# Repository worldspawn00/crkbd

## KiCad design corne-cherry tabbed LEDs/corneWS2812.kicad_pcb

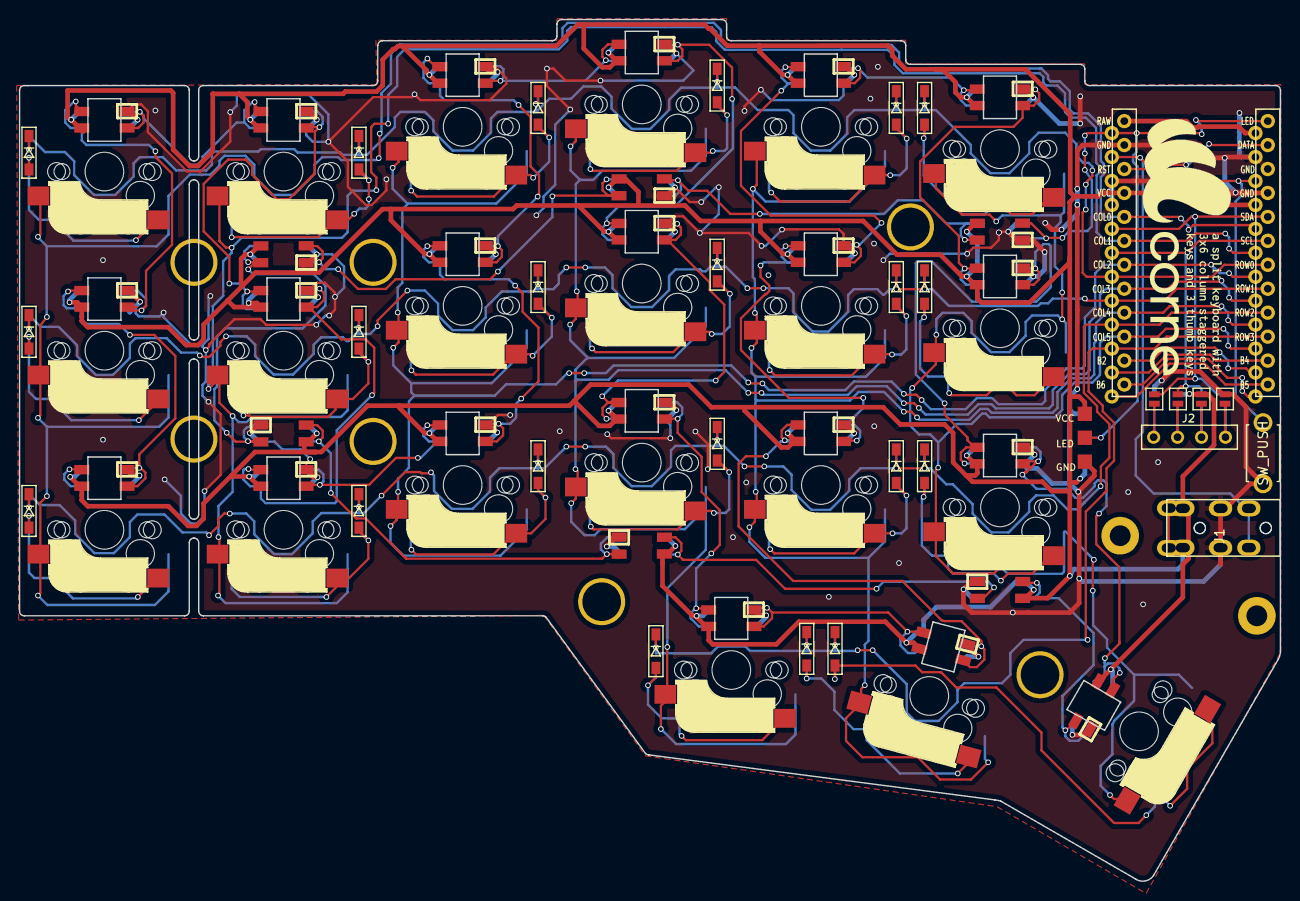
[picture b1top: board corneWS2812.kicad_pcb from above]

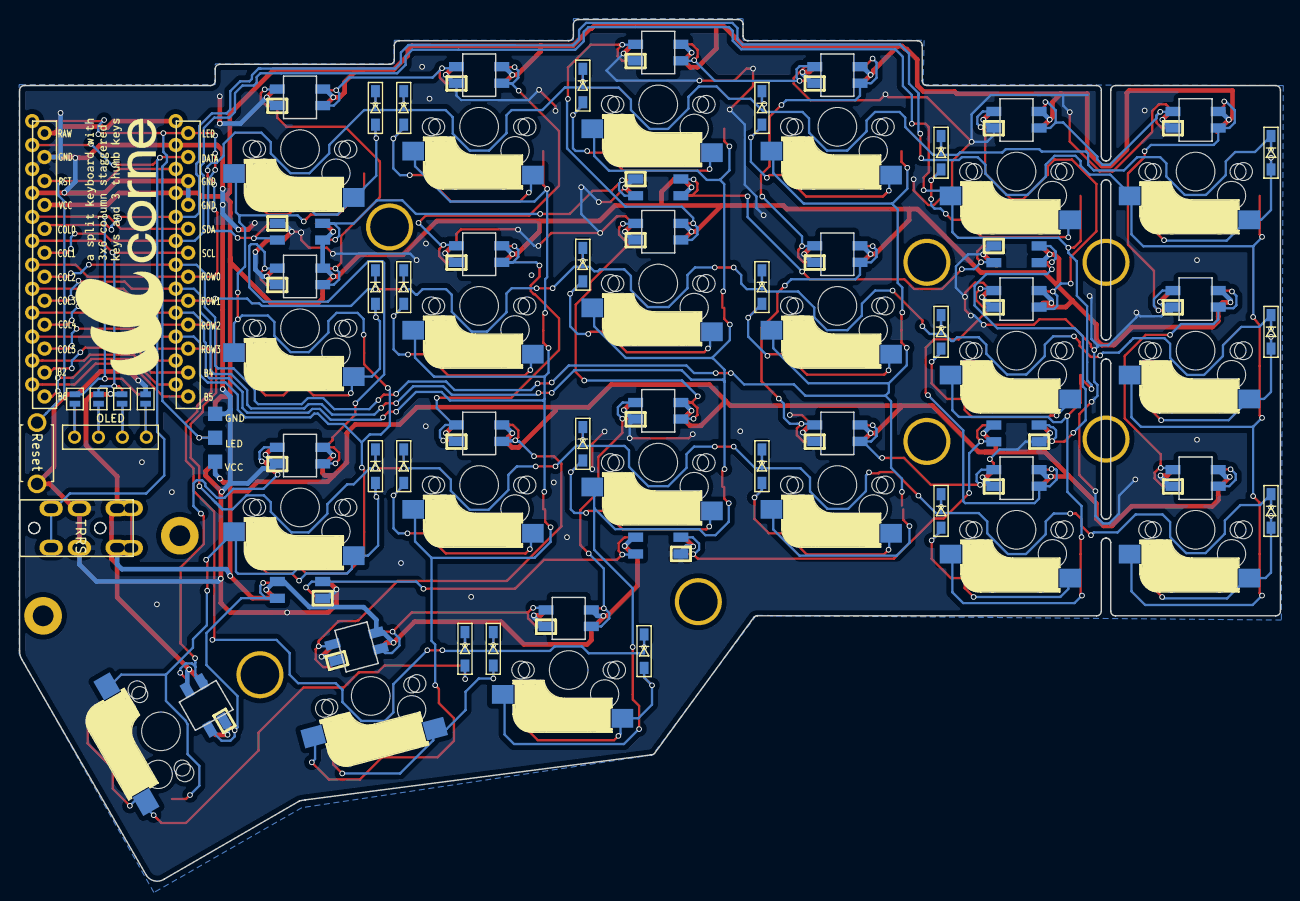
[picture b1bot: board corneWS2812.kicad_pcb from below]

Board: 2 copper layers, 133.8 x 91.4 mm, 82 parts (4 on the bottom side), 68 nets.

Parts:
D1, D2, D3, D4, D5, D6, D7, D8, D9, D10, D11, D12, D13, D14, D15, D16, D17, D18, D19, D20, D21: D; D3_SMD
J1: MJ-4PP-9
J2: OLED
J3: LED; StripLED_rev
JP2, JP3, JP4, JP5, JP6, JP7, JP8, JP9: Jumper
L1, L2, L3, L4, L5, L6, L7, L8, L9, L10, L11, L12, L13, L14, L15, L16, L17, L18, L19, L20, L21: SK6812MINI; WS2812RM
L22, L23, L24, L25, L26, L27: SK6812MINI; WS2812FM
RSW1: SW_PUSH; ResetSW
SW1, SW2, SW3, SW4, SW5, SW6, SW7, SW8, SW9, SW10, SW11, SW12, SW13, SW14, SW15, SW16, SW17, SW18, SW19, SW20: SW_PUSH; CherryMX_MidHeight_Hotswap
SW21: SW_PUSH; CherryMX_MidHeight_Hotswap_1.5u
U1: ProMicro; ProMicro_v2

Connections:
GND: J1.C, J3.1, JP2.1, JP9.1, L1.3, L2.3, L3.3, L4.3, L5.3, L6.3, L7.3, L8.3, L9.3, L10.3, L11.3, L12.3, L13.3, L14.3, L15.3, L16.3, L17.3, L18.3, L19.3, L20.3, L21.3, L22.3, L23.3, L24.3, L25.3, L26.3, L27.3, RSW1.2, U1.3, U1.4, U1.23
LED: J3.2, L24.4, U1.1
unnamed: D1.2, SW1.2
unnamed: D2.2, SW2.2
unnamed: D3.2, SW3.2
unnamed: D4.2, SW4.2
unnamed: D5.2, SW5.2
unnamed: D6.2, SW6.2
unnamed: D7.2, SW7.2
unnamed: D8.2, SW8.2
unnamed: D9.2, SW9.2
unnamed: D10.2, SW10.2
unnamed: D11.2, SW11.2
unnamed: D12.2, SW12.2
unnamed: D13.2, SW13.2
unnamed: D14.2, SW14.2
unnamed: D15.2, SW15.2
unnamed: D16.2, SW16.2
unnamed: D17.2, SW17.2
unnamed: D18.2, SW18.2
unnamed: D19.2, SW19.2
unnamed: D20.2, SW20.2
unnamed: D21.2, SW21.2
unnamed: J2.1, JP5.2, JP9.2
unnamed: J2.2, JP4.2, JP8.2
unnamed: J2.3, JP3.2, JP7.2
unnamed: J2.4, JP2.2, JP6.2
unnamed: L1.2, L7.4
unnamed: L1.4, L2.2
unnamed: L2.4, L8.2
unnamed: L3.2, L9.4
unnamed: L3.4, L4.2
unnamed: L5.4, L6.2
unnamed: L4.4, L10.2
unnamed: L10.4, L16.2
unnamed: L11.2, L17.4
unnamed: L5.2, L11.4
unnamed: L6.4, L12.2
unnamed: L12.4, L18.2
unnamed: L7.2, L13.4
unnamed: L8.4, L14.2
unnamed: L14.4, L15.2
unnamed: L9.2, L15.4
unnamed: L16.4, L19.2
unnamed: L17.2, L20.4
unnamed: L18.4, L21.2
unnamed: L19.4, L20.2
unnamed: L21.4, L27.2
unnamed: L22.2, L25.4
unnamed: L22.4, L23.2
unnamed: L23.4, L24.2
unnamed: L25.2, L26.4
unnamed: L26.2, L27.4
SCL: JP4.1, JP7.1, U1.6
SDA: JP5.1, JP6.1, U1.5
VCC: J1.D, J3.3, JP3.1, JP8.1, L1.1, L2.1, L3.1, L4.1, L5.1, L6.1, L7.1, L8.1, L9.1, L10.1, L11.1, L12.1, L13.1, L14.1, L15.1, L16.1, L17.1, L18.1, L19.1, L20.1, L21.1, L22.1, L23.1, L24.1, L25.1, L26.1, L27.1, U1.21
col0: SW1.1, SW7.1, SW13.1, U1.20
col1: SW2.1, SW8.1, SW14.1, U1.19
col2: SW3.1, SW9.1, SW15.1, U1.18
col3: SW4.1, SW10.1, SW16.1, SW19.1, U1.17
col4: SW5.1, SW11.1, SW17.1, SW20.1, U1.16
col5: SW6.1, SW12.1, SW18.1, SW21.1, U1.15
data: J1.B, U1.2
reset: RSW1.1, U1.22
row0: D1.1, D2.1, D3.1, D4.1, D5.1, D6.1, U1.7
row1: D7.1, D8.1, D9.1, D10.1, D11.1, D12.1, U1.8
row2: D13.1, D14.1, D15.1, D16.1, D17.1, D18.1, U1.9
row3: D19.1, D20.1, D21.1, U1.10

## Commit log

2020-04-25 adding tabbed LED version
2020-04-25 adding files
